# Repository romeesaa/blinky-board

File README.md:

# blinky-board
a  simple pcb board that has LEDS on it. will need to write the firmware to actually make it work but i essentially followed the blinky starter project guide since this is my second ever electronics project and second time designing a pcb board (so proud yay) 

the guide I used: https://blueprint.hackclub.com/starter-projects/blinky 

# the final look

# the struggles
1) random DRC errors that caused me to change the shape of my pcb board
2) routing (took me some time to figure out u can use two layers but we ball)
3) showing a cute shape and (whatever changed it anyways)
4) trying to import the foot prints (i am stupid)
5) connecting the schematic (grateful that i got no errors this time)

the shape before i got lazy and gave up because of the errors
:( 

the schematic 

the pcb routing (idk whats this called yet..)

an easter egg :

# bom

| #  | Component              | Specification       | Qty.     | Price (PKR) | Purchase link                                                                                        |
| -- | ---------------------- | ------------------- | -------- | ----------- | ---------------------------------------------------------------------------------------------------- |
| 1  | 555 Timer IC           | NE555P, DIP-8       | 1        | 30          | [Pak Modules](https://pakmodules.com/?utm_source=chatgpt.com)                                        |
| 2  | Decade Counter IC      | CD4017, DIP-16      | 1        | 65          | [Electronic Store](https://electronicstore.pk/product/cd4017-ic-in-pakistan/?utm_source=chatgpt.com) |
| 3  | Red LEDs               | 5mm through-hole    | 10       | 30          | [Electronation](https://electronation.pk/product-category/common-components/?utm_source=chatgpt.com) |
| 4  | Orange LEDs            | 5mm through-hole    | Optional | 3 each      | [Electronation](https://electronation.pk/product-category/common-components/?utm_source=chatgpt.com) |
| 5  | Yellow LEDs            | 5mm through-hole    | Optional | 3 each      | [Electronation](https://electronation.pk/product-category/common-components/?utm_source=chatgpt.com) |
| 6  | Green LEDs             | 5mm through-hole    | Optional | 3 each      | [Electronation](https://electronation.pk/product-category/common-components/?utm_source=chatgpt.com) |
| 7  | Blue LEDs              | 5mm through-hole    | Optional | 3 each      | [Electronation](https://electronation.pk/product-category/common-components/?utm_source=chatgpt.com) |
| 8  | Resistor               | 1 kΩ, ¼ W           | 1        | 2–5         | [Electronation](https://electronation.pk/product-category/common-components/?utm_source=chatgpt.com) |
| 9  | Resistor               | 470 Ω, ¼ W          | 1        | 2–5         | [Circuit.pk](https://circuit.pk/category/resistor?utm_source=chatgpt.com)                            |
| 10 | Potentiometer          | 50 kΩ               | 1        | 10          | [Electronation](https://electronation.pk/product-category/common-components/?utm_source=chatgpt.com) |
| 11 | Electrolytic capacitor | 1 µF                | 1        | 5–10\*      | [Electronic Store](https://electronicstore.pk/product-category/capacitor/?utm_source=chatgpt.com)    |
| 12 | Ceramic capacitor      | 10 nF               | 1        | 5–10\*      | [Electronic Store](https://electronicstore.pk/product-category/capacitor/?utm_source=chatgpt.com)    |
| 13 | 2-pin connector        | PCB power connector | 1        | 10–20\*     | [Electronic Store](https://electronicstore.pk/product-category/connector/?utm_source=chatgpt.com)    |
| 14 | 1-pin header           | Debug output        | 1        | 5–10\*      | [Electronic Store](https://electronicstore.pk/product-category/connector/?utm_source=chatgpt.com)    |

| # | Item           | Specification       | Qty.      | Estimated price (PKR) | Purchase link                                                                                                       |
| - | -------------- | ------------------- | --------- | --------------------- | ------------------------------------------------------------------------------------------------------------------- |
| 1 | Power supply   | Regulated 5V USB    | 1         | 250–400               | [Electronic Store](https://electronicstore.pk/product-category/battery-charger-powersupply/?utm_source=chatgpt.com) |
| 2 | PCB            | Custom-designed PCB | 1         | Not yet quoted        | [JLCPCB](https://jlcpcb.com/?utm_source=chatgpt.com)                                                                |
| 3 | IC socket      | 8-pin DIP           | 1         | 10–15                 | [Electronic Store](https://electronicstore.pk/product-category/ic-socket-base/?utm_source=chatgpt.com)              |
| 4 | IC socket      | 16-pin DIP          | 1         | 15–25                 | [Electronic Store](https://electronicstore.pk/product-category/ic-socket-base/?utm_source=chatgpt.com)              |
| 5 | Soldering wire | Electronics solder  | As needed | 150–250               | [Pak Modules](https://pakmodules.com/?utm_source=chatgpt.com)                                                       |
| 6 | Jumper wires   | Testing/debugging   | A few     | 50–100                | [Electronic Store](https://electronicstore.pk/product-category/jumper-wire-crimshell/?utm_source=chatgpt.com)       |

funding needed : 1000-2000 rs or (3.61 US Dollars to 7.22 US Dollars to cover the shipping costs and everything)

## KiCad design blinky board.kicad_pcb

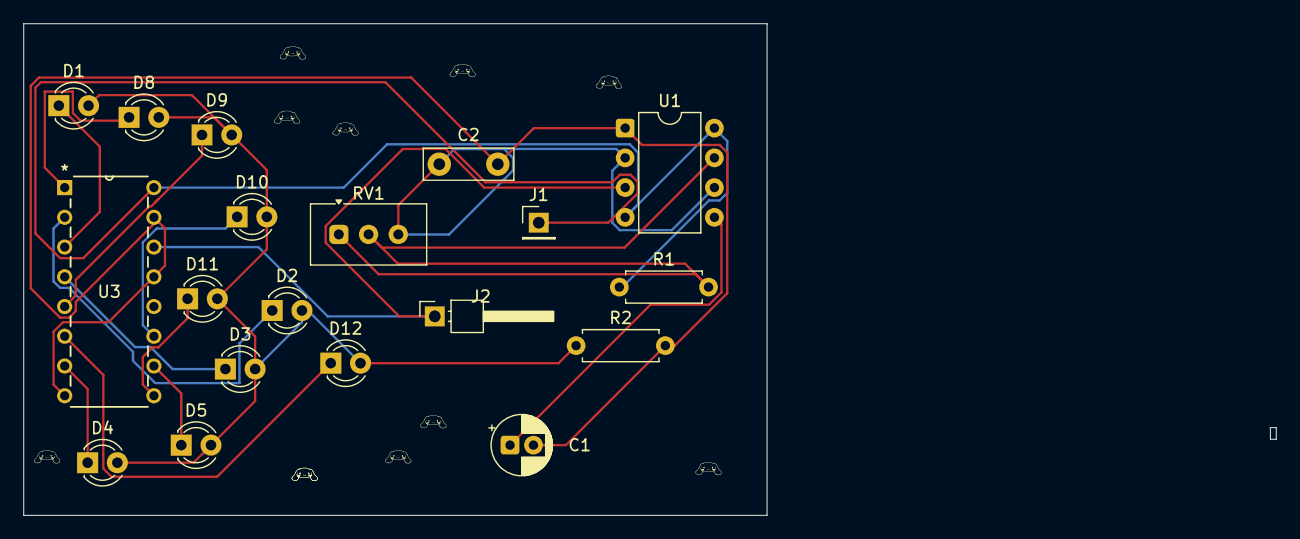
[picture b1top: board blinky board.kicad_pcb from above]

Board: 2 copper layers, 63.5 x 42.0 mm, 19 parts (0 on the bottom side), 17 nets.

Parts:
C1: 0.01 uf; CP_Radial_D5.0mm_P2.00mm
C2: 1 uf; C_Disc_D7.5mm_W2.5mm_P5.00mm
D1, D2, D3, D4, D5, D8, D9, D10, D11, D12: LED; LED_D3.0mm
J1: Conn_01x02_Socket; PinHeader_1x01_P2.54mm_Vertical
J2: Conn_01x01_Socket; PinHeader_1x01_P2.54mm_Horizontal
R1: 1k; R_Axial_DIN0207_L6.3mm_D2.5mm_P7.62mm_Horizontal
R2: 470; R_Axial_DIN0207_L6.3mm_D2.5mm_P7.62mm_Horizontal
RV1: 50k; Potentiometer_Vishay_T93YA_Vertical
U1: NE555P; DIP-8_W7.62mm
U3: 4017; N16

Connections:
+5V: J1.1 (Pin_1_1), R1.1, U1.4 (~RST), U1.8 (VCC), U3.16 (VDD)
/OUT: J2.1 (Pin_1_1), U1.3 (OUT), U3.14 (CLK)
/TR: C2.1, RV1.3, U1.2 (TRIG), U1.6 (THRES)
GND: C1.2, C2.2, R2.2, U1.1 (GND), U3.8 (VSS), U3.13 (CKEN), U3.15 (Reset)
unnamed: D1.2 (A), D2.2 (A), D3.2 (A), D4.2 (A), D5.2 (A), D8.2 (A), D9.2 (A), D10.2 (A), D11.2 (A), D12.2 (A), R2.1
unnamed: D1.1 (K), U3.3 (Q0)
unnamed: D2.1 (K), U3.2 (Q1)
unnamed: D3.1 (K), U3.4 (Q2)
unnamed: D4.1 (K), U3.7 (Q3)
unnamed: D5.1 (K), U3.10 (Q4)
unnamed: D8.1 (K), U3.1 (Q5)
unnamed: D9.1 (K), U3.5 (Q6)
unnamed: D10.1 (K), U3.11 (Q9)
unnamed: D11.1 (K), U3.9 (Q8)
unnamed: D12.1 (K), U3.6 (Q7)
unnamed: C1.1, U1.5 (CONT)
unnamed: R1.2, RV1.1, RV1.2, U1.7 (DISCH)
